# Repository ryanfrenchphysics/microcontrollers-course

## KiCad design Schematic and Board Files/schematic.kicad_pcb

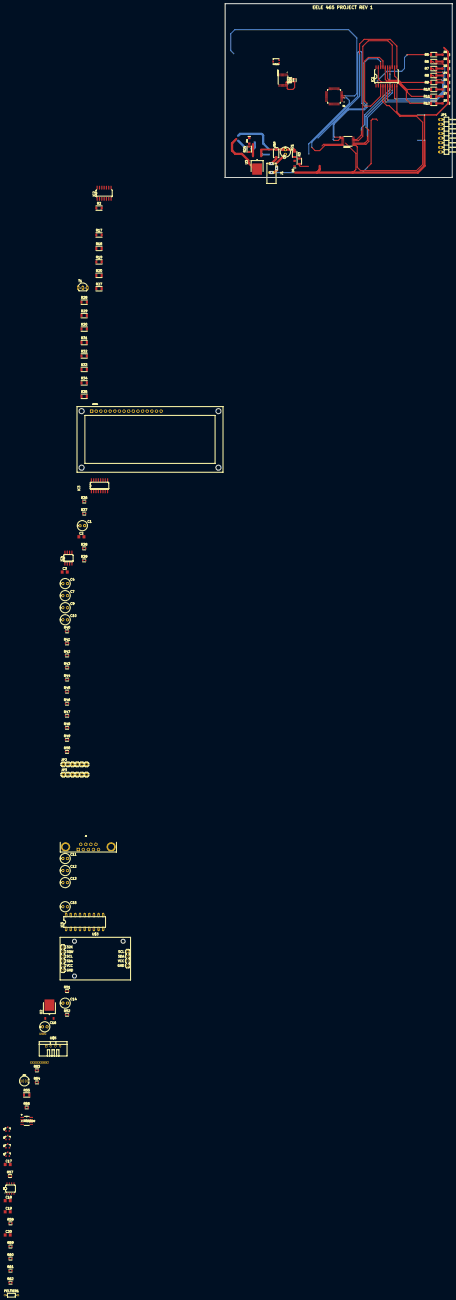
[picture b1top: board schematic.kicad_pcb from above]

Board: 2 copper layers, 124.5 x 95.2 mm, 119 parts (0 on the bottom side), 101 nets.

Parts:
C1, C4, C7, C9: 10u; E2,5-6E
C2, C3, C5, C6, C20: 0.1u; C1206
C8: 1000u; E2,5-6E
C10, C11, C12, C13, C14, C15: 0.1u; E2,5-6E
C16: 0.33u; E2,5-6E
C17: 470p; C1206
C18, C19: 10n; C1206
D1, D2, D3, D4, D5, D6, D7, D8, D11: RED; LED-1206
D9: GREEN; LED-1206
D10: DIODE-SCHOTTKY-SS14; SMA-DIODE
D12: CLEAR; LED-RGB-THRU
IC1: 74273DW; SO20W
IC2: 7432D; SO14
IC3: 74174D; SO16
IC4: ICL7660CSA; SO08
IC5: MAX3222; DIL18
IC6: OP-AMP; SO08
J1: 694103303002
J2: DB9FEMALE; DB9
JP1: PINHD-1X8_90; 1X08_90
JP2, JP3: PINHD-1X6; 1X06
LCD1: LCD-16X2SILK; LCD-16X2
PELTIER1: R-USAXIAL-7.2MM-PITCH; RESAD724W46L381D178B
Q1, Q2: TRANS_NPN-MMBT2222AL; SOT23-3
Q3, Q4: TRANS_PNP-MMBT4403; SOT23-3
R1, R37, R51, R52, R53, R54, R56, R59, R61, R62: 10k; RESC1608X60
R2, R3, R15, R17, R18, R21: 10k; RESC3216X70
R5, R6, R7, R8, R9, R10, R11, R12, R27: 470; RESC3216X70
R19, R20: 4.7k; RESC3216X70
R22, R23, R25, R26: 4.7k; RESC1608X60
R24: 160; RESC3216X70
R28, R29, R30, R31, R32, R33, R34, R35: 1k; RESC3216X70
R36: 680; RESC1608X60
R38, R39, R40, R41, R42, R43, R44, R45, R46, R47, R48, R49, R50: 1k; RESC1608X60
R55: 120; RESC3216X70
R57, R60: 15; RESC1608X60
R58: 0.02; RESC1608X60
T1: 2N2222; TO92-EBC-OVAL
U1: MSP430FR2355TPT; QFP50P900X900X160-48N
U2, U3: +12v; TO-252
U4: INA155U; D8
U$1, U$2: MSP430FR2310; SOP65P640X120-16N
U$3: DS3231; RTC-DS3231-AT24C32
U$4: LM19
U$5: DHT22; TEMP-HUM-SENSOR-DHT22
U$6: LM92
VR1: 20k; TRIMPOT-SMD-3MM-CLOSED

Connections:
5V: C5.1, C8.+, C16.+, D10.C, R21.2, U2.1, U3.1
/DHT22-DAT: R56.1, U$5.2
/KEY_COL1: R2.1, U1.41
/KEY_COL2: R15.1, U1.36
/KEY_COL3: R17.1, U1.29
/KEY_COL4: R18.1, U1.30
/KEY_INT: R27.1, U1.47
/KEY_ROW1: JP1.1, U1.45
/KEY_ROW2: JP1.2, U1.46
/KEY_ROW3: JP1.3, U1.38
/KEY_ROW4: JP1.4, U1.14
/LED_RST: T1.B, U1.44
/LM19: U1.2, U$4.P$3
/NEG_3V3: C9.-, IC4.5, VR1.3
/RS232_RX: IC5.12, U1.32
/RS232_TX: IC5.13, U1.31
/RST: JP2.3, JP3.3, R1.1, R3.1, R37.1, T1.C, U1.5, U$1.4, U$2.4
/SCL: JP2.6, JP3.6, R20.1, R22.1, R26.1, R52.1, R54.1, U1.12, U$1.15, U$2.15, U$3.J1.3, U$6.P$6
/SDA: JP2.5, JP3.5, R19.1, R23.1, R25.1, R51.1, R53.1, U1.13, U$1.16, U$2.16, U$3.J1.4, U$6.P$7
/TEC_PIN: IC6.3, U1.22
/V_BIAS_LCD: LCD1.3, VR1.2
GND: C1.-, C2.2, C3.2, C4.-, C5.2, C6.2, C8.-, C9.+, C10.-, C12.-, C14.-, C15.+, C16.-, C18.2, C19.2, D1.C, D2.C, D3.C, D4.C, D5.C, D6.C, D7.C, D8.C, D9.C, D11.C, IC1.10, IC2.2, IC2.5, IC2.7, IC2.10, IC2.13, IC3.8, IC4.3, IC4.6, IC5.1, IC5.8, IC5.9, IC5.10, IC5.11, IC5.16, IC6.5, J1.2, J1.3, J2.5, JP2.2, JP3.2, LCD1.1, R28.1, R29.1, R30.1, R31.1, R32.1, R33.1, R34.1, R35.1, R38.1, R39.1, R40.2, R41.2, R42.2, R43.2, R44.2, R45.2, R46.2, R47.2, R48.2, R49.2, R50.2, R55.1, T1.E, U1.7, U2.3, U3.3, U4.5, U$1.6, U$2.6, U$3.J1.6, U$3.J2.1, U$3.J2.2, U$3.J2.3, U$3.J2.4, U$4.P$1, U$5.4, U$6.P$2, U$6.P$3, U$6.P$4
unnamed: C3.1, C4.+, U$2.5
unnamed: C7.+, IC4.2
unnamed: C7.-, IC4.4
unnamed: C11.+, IC5.2
unnamed: C11.-, IC5.4
unnamed: C12.+, IC5.3
unnamed: C13.+, IC5.5
unnamed: C13.-, IC5.6
unnamed: C14.+, U1.3, U2.2
unnamed: C15.-, IC5.7
unnamed: C17.1, IC6.7, R60.2
unnamed: C17.2, IC6.6, R61.2, R62.1
unnamed: C20.1, IC6.1, R57.2
unnamed: C20.2, IC6.2, R59.2
unnamed: D1.A, R5.2
unnamed: D2.A, R6.2
unnamed: D3.A, R7.2
unnamed: D4.A, R8.2
unnamed: D5.A, R9.2
unnamed: D6.A, R10.2
unnamed: D7.A, R11.2
unnamed: D8.A, R12.2
unnamed: D9.A, R21.1
unnamed: D10.A, J1.1
unnamed: D11.A, R24.2
unnamed: D12.1, U1.19
unnamed: D12.2, R55.2
unnamed: D12.3, U1.21
unnamed: D12.4, U1.20
unnamed: IC1.2, R5.1
unnamed: IC1.3, R32.2, U$1.8
unnamed: IC1.4, R31.2, U$1.9
unnamed: IC1.5, R6.1
unnamed: IC1.6, R7.1
unnamed: IC1.7, R30.2, U$1.10
unnamed: IC1.8, R28.2, U$1.11
unnamed: IC1.9, R8.1
unnamed: IC1.11, U$1.7
unnamed: IC1.12, R9.1
unnamed: IC1.13, R29.2, U$1.13
unnamed: IC1.14, R33.2, U$1.14
unnamed: IC1.15, R10.1
unnamed: IC1.16, R11.1
unnamed: IC1.17, R34.2, U$1.1
unnamed: IC1.18, R35.2, U$1.2
unnamed: IC1.19, R12.1
unnamed: IC2.1, JP1.8, R2.2
unnamed: IC2.4, JP1.7, R15.2
unnamed: IC2.9, JP1.6, R17.2
unnamed: IC2.3, IC2.6, IC2.8, IC2.11, R27.2
unnamed: IC2.12, JP1.5, R18.2
unnamed: IC3.1, R36.1
unnamed: IC3.2, LCD1.7, R43.1
unnamed: IC3.3, LCD1.12, R48.1, U$2.1
unnamed: IC3.4, LCD1.13, R49.1, U$2.10
unnamed: IC3.5, LCD1.8, R44.1
unnamed: IC3.6, LCD1.11, R47.1, U$2.8
unnamed: IC3.7, LCD1.9, R45.1
unnamed: IC3.9, U$2.9
unnamed: IC3.10, LCD1.10, R46.1
unnamed: IC3.11, LCD1.14, R50.1, U$2.2
unnamed: IC3.13, R39.2
unnamed: IC3.14, R38.2
unnamed: IC5.14, J2.3
unnamed: IC5.15, J2.2
unnamed: JP2.4, JP3.4, U$2.3
unnamed: LCD1.4, R40.1, U$2.14
unnamed: LCD1.5, R41.1, U$2.13
unnamed: LCD1.6, R42.1, U$2.11
unnamed: PELTIER1.1, R58.1, R61.1, U4.2
unnamed: PELTIER1.2, Q2.2, Q4.2, R62.2
unnamed: Q1.1, Q3.1, R57.1
unnamed: Q1.2, Q3.2, R58.2, U4.3
unnamed: Q2.1, Q4.1, R60.1
unnamed: R59.1, U4.6
unnamed: U4.1, U4.8
VCC: IC1.20, IC2.14, IC3.16, IC5.17
VDD: C1.+, C2.1, C6.1, C10.+, C18.1, IC4.8, IC5.18, IC6.8, JP2.1, JP3.1, LCD1.2, Q1.3, Q2.3, R1.2, R3.2, R19.2, R20.2, R22.2, R23.2, R24.1, R25.2, R26.2, R36.2, R37.2, R51.2, R52.2, R53.2, R54.2, R56.2, U1.6, U3.2, U4.7, U$1.5, U$3.J1.5, U$4.P$2, U$5.1, U$6.P$1, VR1.1
VIN: C19.1, IC6.4, Q3.3, Q4.3, U4.4

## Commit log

2020-12-01 First commit. Added all the stuff I had on my local machine.
2020-12-01 Removed large MP4 files
